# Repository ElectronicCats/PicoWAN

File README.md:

# PicoWAN

PicoWAN is all the best in the world format Feather and LoRa with a Raspberry Pico Core!, Feather pin to pin compatible with a USB-C port.

We love all our Feathers equally, but this Feather is very special. It's our first Feather that is specifically designed for use with CircuitPython! CircuitPython is our beginner-oriented flavor of MicroPython - and as the name hints at, its a small but full-featured version of the popular Python programming language specifically for use with circuitry and electronics.

Please note, CircuitPython does not come preloaded. See the full guide linked below for instructions on installing it

# License

Electronic Cats invests time and resources providing this open source design, please support Electronic Cats and open-source hardware by purchasing products from Electronic Cats!

Designed by Electronic Cats.

Firmware released under an GNU AGPL v3.0 license. See the LICENSE file for more information.

Hardware released under an CERN Open Hardware Licence v1.2. See the LICENSE_HARDWARE file for more information.

Electronic Cats is a registered trademark, please do not use if you sell these PCBs.

January 2020

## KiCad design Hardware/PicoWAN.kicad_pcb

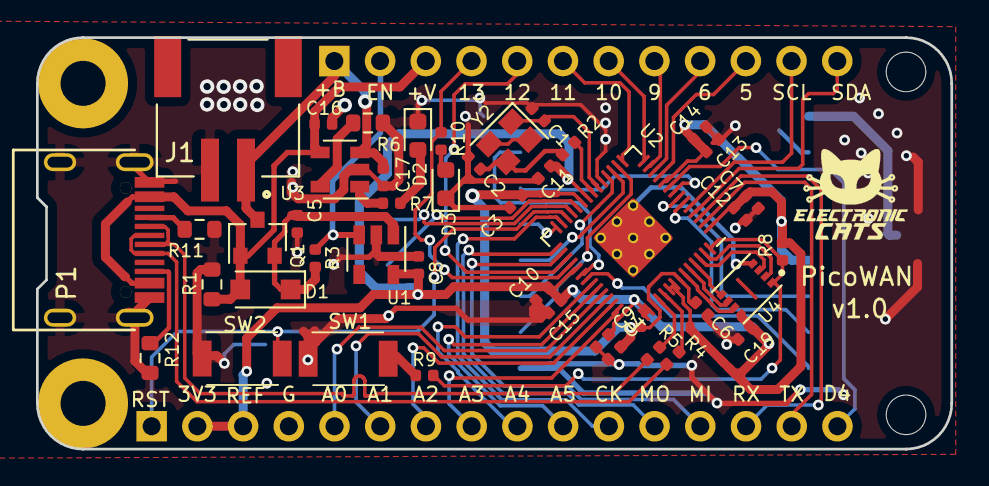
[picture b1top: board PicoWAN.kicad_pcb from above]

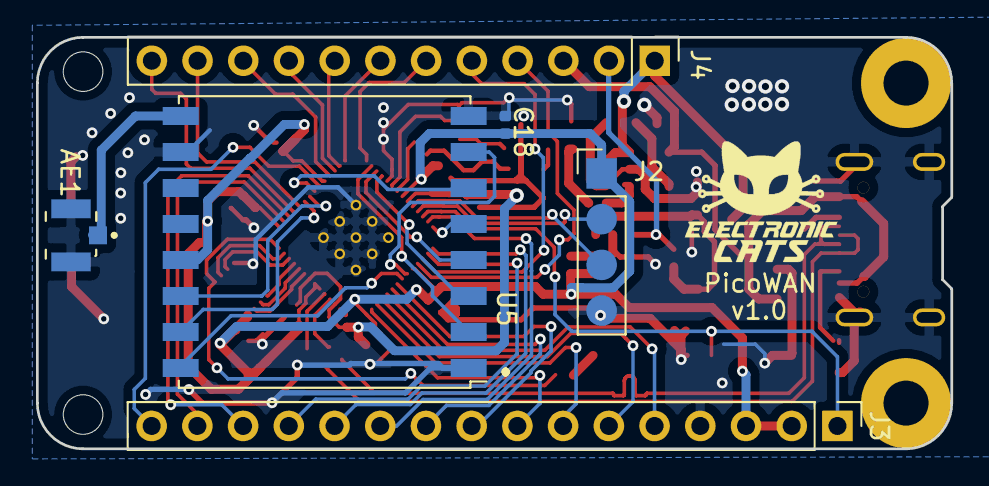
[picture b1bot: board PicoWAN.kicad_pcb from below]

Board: 2 copper layers, 50.8 x 22.9 mm, 49 parts (6 on the bottom side), 61 nets.

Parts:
AE1: Antenna_Shield; MOLEX_1661
C1, C2: 22pF; C_0402_1005Metric
C3, C7, C8: 1uF; C_0402_1005Metric
C4, C6, C9, C10, C11, C12, C13, C14, C15, C18, C19: 0.1uF; C_0402_1005Metric
C5: 4.7uF; C_0402_1005Metric
C16, C17: 10uF; C_0402_1005Metric
D1: MBR120; D_SOD-123F
D2: BAT; LED_0603_1608Metric
D3: LED; LED_0603_1608Metric
J1: Battery; JST_S2B-PH-SM4-TB(LF)(SN)
J2: SWD; PinHeader_1x04_P2.54mm_Vertical
J3: Conn_left; PinHeader_1x16_P2.54mm_Vertical
J4: Conn_right; PinHeader_1x12_P2.54mm_Vertical
P1: USB_C_Plug_USB2.0; C393939
Q1: DMG3415U-7; SOT-23
R1: 100K; R_0603_1608Metric
R2, R7, R9: 1K; R_0402_1005Metric
R3, R8, R10: 10K; R_0402_1005Metric
R4, R5: 27; R_0402_1005Metric
R6: 2K; R_0603_1608Metric
R11, R12: 5K1; R_0603_1608Metric
SW1: BOOT; TS1088R02026
SW2: RESET; TS1088R02026
U1: AP2112K-3.3; SOT-23-5
U2: RP2040; RP2040-QFN-56
U3: MCP73831-2-OT; SOT-23-5
U4: W25Q16JV; PSON50P200X300X50-9N
U5: RFM95W-868S2; HOPERF_RFM9XW_SMD
Y2: 12Mhz; Crystal_SMD_2520-4Pin_2.5x2.0mm

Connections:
+1V2: C3.1, C4.1, C6.1, U2.23, U2.45, U2.50
+3V3: C7.1, C8.1, C9.1, C10.1, C11.1, C12.1, C13.1, C14.1, C15.1, C18.1, C19.1, J2.1, J3.2, J3.3, R8.1, U1.5, U2.1, U2.10, U2.22, U2.33, U2.42, U2.43, U2.44, U2.48, U2.49, U4.8, U5.13
+BATT: C17.1, J1.1, J4.1, Q1.3, U3.3
/A0: J3.5, U2.38
/A1: J3.6, U2.39
/A2: J3.7, U2.40
/A3: J3.8, U2.41
/CIPO_0: J3.11, U2.27
/CIPO_1: U2.16, U5.2
/COPI_0: J3.13, U2.30
/COPI_1: U2.18, U5.3
/CS_1: U2.28, U5.5
/D4: J3.16, U2.9
/D5: J4.10, U2.11
/D6: J4.9, U2.12
/D9: J4.8, U2.13
/D10: J4.7, U2.14
/D11: J4.6, U2.15
/D12: J4.5, U2.31
/D13: J4.4, R10.2, U2.32
/D24: J3.9, U2.36
/D25: J3.10, U2.37
/D+: P1.A6, R4.1
/D-: P1.A7, R5.1
/DIO0: U2.7, U5.14
/DIO1: U2.6, U5.15
/DIO2: U2.35, U5.16
/DIO5: U2.34, U5.7
/EN: J4.2, R3.2, U1.3
/QSPI_CS: R8.2, R9.1, U2.56, U4.1
/QSPI_DATA0: U2.53, U4.5
/QSPI_DATA1: U2.55, U4.2
/QSPI_DATA2: U2.54, U4.3
/QSPI_DATA3: U2.51, U4.7
/QSPI_SCK: U2.52, U4.6
/RD+: R4.2, U2.47
/RD-: R5.2, U2.46
/RF_RST: U2.8, U5.6
/RST: J3.1, SW2.2, U2.26
/RX: J3.14, U2.3
/SCK_0: J3.12, U2.29
/SCK_1: U2.17, U5.4
/SCL: J4.11, U2.5
/SDA: J4.12, U2.4
/SWCLK: J2.3, U2.24
/SWDIO: J2.2, U2.25
/TX: J3.15, U2.2
GND: AE1.2, C1.2, C2.2, C3.2, C4.2, C5.2, C6.2, C7.2, C8.2, C9.2, C10.2, C11.2, C12.2, C13.2, C14.2, C15.2, C16.2, C17.2, C18.2, C19.2, D2.1, D3.1, J1.2, J2.4, J3.4, P1.A1, P1.S1, R1.2, R6.2, R11.1, R12.1, SW1.1, SW2.1, U1.2, U2.19, U2.57, U3.2, U4.4, U5.1, U5.8, U5.10, Y2.2
unnamed: AE1.1, U5.9
unnamed: C1.1, U2.20, Y2.1
unnamed: C2.1, R2.1, Y2.3
unnamed: C5.1, D1.1, Q1.2, R3.1, U1.1
unnamed: D2.2, R7.2
unnamed: D3.2, R10.1
unnamed: P1.A5, R11.2
unnamed: P1.B5, R12.2
unnamed: R2.2, U2.21
unnamed: R6.1, U3.5
unnamed: R7.1, U3.1
unnamed: R9.2, SW1.2
VBUS: C16.1, D1.2, J4.3, P1.A4, Q1.1, R1.1, U3.4

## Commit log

2021-01-30 init schematic
2021-01-30 add feather format
2021-01-30 Create LICENSE
2021-01-30 add caps and added new pins
2021-01-30 init select footprints
2021-01-30 update to 0603
2021-01-31 update footprint RP2040
2021-02-02 add libraries intialize floor plan
2021-02-23 Change_footprint
2021-02-26 Init_rout
2021-02-26 Last_Change
2021-02-27 Route
2021-02-28 add logo and labels
2021-03-02 Move_Micro
2021-03-02 Add_GND
2021-03-02 Add_Fottprint
2021-03-02 Add_track
2021-03-02 add logo front
2021-03-02 Add_Labels
2021-03-04 fix traces
2021-03-04 update crystal and traces
2021-03-05 Add_BOM
2021-03-05 Add_RFM_BOM
2021-03-06 Add_Bat conector_BOM
2021-08-24 chgSPIpins
2021-08-24 nRouteinProgress
2021-08-26 RoutedPCB
2021-09-08 Correction_Tracks
2022-01-07 Update_kicad_6
2022-07-16 change pins SPI ok
